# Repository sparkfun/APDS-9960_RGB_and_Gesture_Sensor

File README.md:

SparkFun APDS-9960 RGB and Gesture Sensor
========================================

[*SparkFun APDS-9960 Breakout Board (SEN-12787)*](https://www.sparkfun.com/products/12787)

This is the SparkFun RGB and Gesture Sensor, a small breakout board with a built in APDS-9960 sensor that offers ambient light and color measuring, proximity detection, and touchless gesture sensing.
With this RGB and Gesture Sensor you will be able to control a computer, microcontroller, robot, and more with a simple swipe of your hand! 

 Repository Contents
-------------------

* **/Hardware** - Eagle design files (.brd, .sch)
* **/Libraries** - Libraries for use with the SparkFun APDS9960 RGB and Gesture Sensor
* **/Production** - Production panel files (.brd)

Documentation
--------------
* **[Quickstart Guide](https://learn.sparkfun.com/tutorials/apds-9960-rgb-and-gesture-sensor-hookup-guide)** - Basic hookup guide for the sensor.
* **[Library/README](https://github.com/sparkfun/SparkFun_APDS-9960_Sensor_Arduino_Library/tree/V_1.4.1)** - Arduino library for the SparkFun_APDS9960 RGB and Gesture Sensor.
* **[SparkFun Fritzing repo](https://github.com/sparkfun/Fritzing_Parts)** - Fritzing diagrams for SparkFun products.
* **[SparkFun 3D Model repo](https://github.com/sparkfun/3D_Models)** - 3D models of SparkFun products. 

Product Versions
----------------
* **[SEN-12787](https://www.sparkfun.com/products/12787)** - APDS-9960 RGB and Gesture Sensor

Version History
---------------
* [V_H1.0_L1.4.2](https://github.com/sparkfun/APDS-9960_RGB_and_Gesture_Sensor/tree/V_H1.0_L1.4.2) - Fixing library name compiliation error. 
* [V_H1.0_L1.4.1](https://github.com/sparkfun/APDS-9960_RGB_and_Gesture_Sensor/tree/V_H1.0_L1.4.1) - Fixing minor typos in both library and hardware files.
* [V_1.1.1](https://github.com/sparkfun/APDS-9960_RGB_and_Gesture_Sensor/tree/V_1.1.1) - Updated to new tag syntax
* [V11](https://github.com/sparkfun/APDS-9960_RGB_and_Gesture_Sensor/tree/v11) - Updated to new library structure
* [v10](https://github.com/sparkfun/APDS-9960_RGB_and_Gesture_Sensor/tree/v10) - Release
* [v01](https://github.com/sparkfun/APDS-9960_RGB_and_Gesture_Sensor/tree/v01)

License Information
-------------------
This product is _**open source**_! 

The **hardware** is released under [Creative Commons ShareAlike 4.0 International](https://creativecommons.org/licenses/by-sa/4.0/).

The **code** is beerware; if you see me (or any other SparkFun employee) at the local, and you've found our code helpful, please buy us a round!

Please use, reuse, and modify these files as you see fit. Please maintain attribution to SparkFun Electronics and release anything derivative under the same license.

Distributed as-is; no warranty is given.

- Your friends at SparkFun.

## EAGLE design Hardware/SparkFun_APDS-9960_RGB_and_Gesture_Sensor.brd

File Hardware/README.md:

# What Are these Files?

The .sch and .brd files hare are Eagle CAD schematic and PCB design files.

These files were created with Eagle 6.5.0, you'll need Eagle 6.5 or later to open them up. There is a free, lite, version of Eagle available from [cadsoftusa.com](cadsoftusa.com).

# License

This product is open source! These Eagle files are released under the Creative Commons Share-Alike Attribution license ([CC BY-SA 3.0](http://creativecommons.org/licenses/by-sa/3.0/us/)).

Please use, reuse, and modify these files as you see fit. Please maintain attribution and release anything derivative under the same license.

- Your friends at SparkFun.

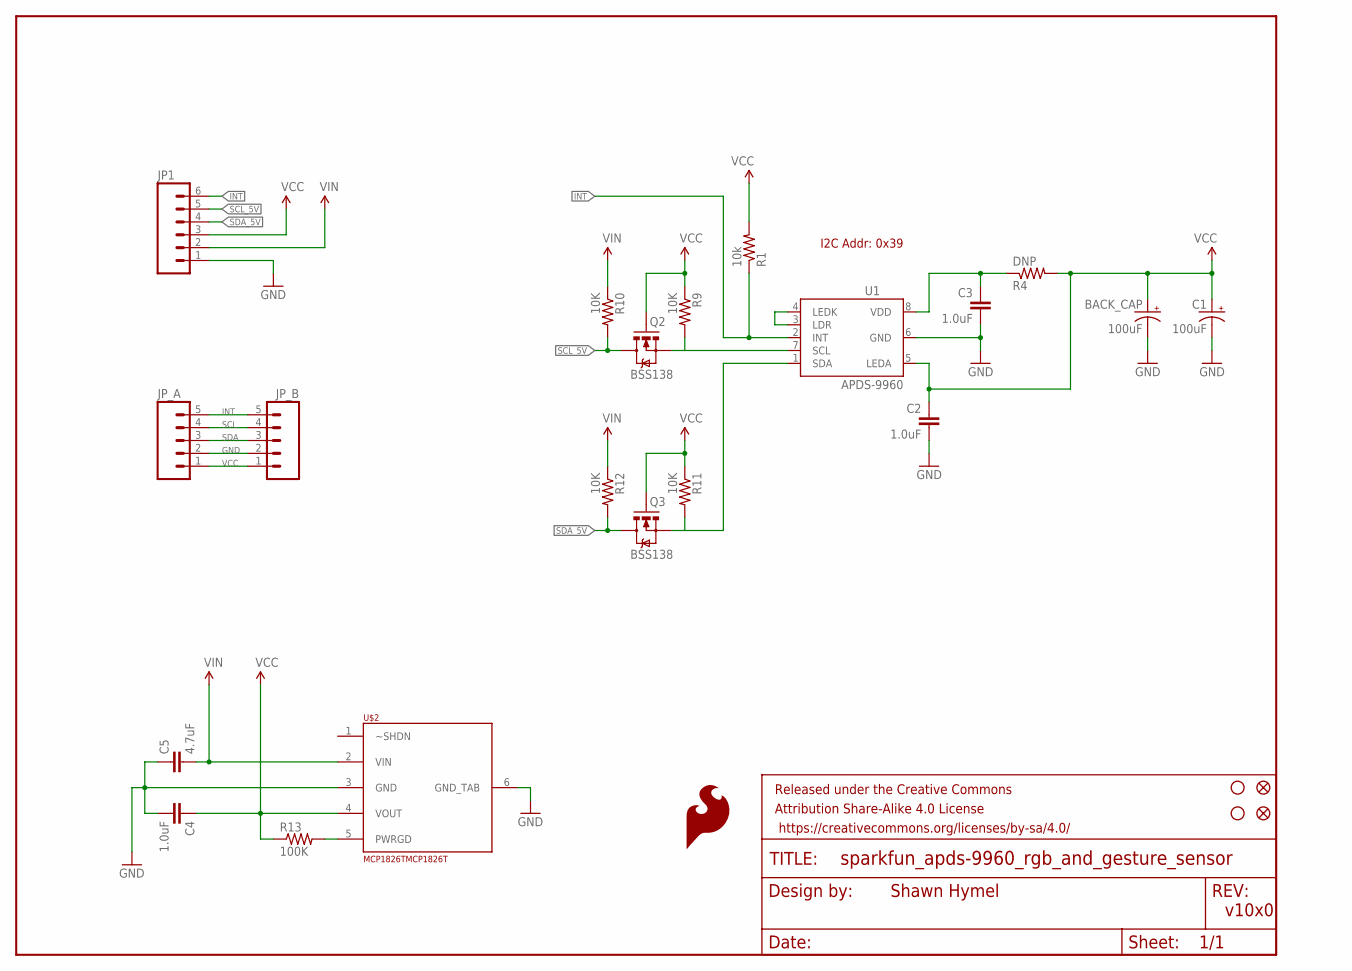
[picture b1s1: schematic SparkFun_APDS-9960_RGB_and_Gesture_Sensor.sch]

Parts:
BACK_CAP: 100uF; EIA7343
C1: 100uF; EIA7343
C2, C3, C4: 1.0uF; 0603-CAP
C5: 4.7uF; 0603-CAP
FID1, FID2: FIDUCIAL1X2; FIDUCIAL-1X2
FRAME1: FRAME-LETTER; CREATIVE_COMMONS
JP1: M06SIP; 1X06
JP_A: M05PTH; 1X05
JP_B: M05PTH; 1X05
LOGO1: SFE_LOGO_FLAME.1_INCH; SFE_LOGO_FLAME_.1
Q2, Q3: BSS138; SOT23-3
R1: 10k; 0603-RES
R4: DNP; 0603-RES
R9, R10, R11, R12: 10K; 0603-RES
R13: 100K; 0603-RES
STANDOFF1, STANDOFF2: STAND-OFF
U1: APDS-9960
U$2: MCP1826TMCP1826T; SOP-223-5

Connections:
GND: BACK_CAP.C (-), C1.C (-), C2.2, C3.2, C4.2, C5.1, JP1.1, JP_A.2, JP_B.2, U1.6 (GND), U$2.3 (GND), U$2.6 (GND_TAB)
INT: JP1.6, JP_A.5, JP_B.5, R1.1, U1.2 (INT)
unnamed: C3.1, R4.1, U1.8 (VDD)
unnamed: U1.3 (LDR), U1.4 (LEDK)
unnamed: R13.2, U$2.5 (PWRGD)
SCL: JP_A.4, JP_B.4, Q2.2 (S), R9.2, U1.7 (SCL)
SCL_5V: JP1.5, Q2.3 (D), R10.2
SDA: JP_A.3, JP_B.3, Q3.2 (S), R11.2, U1.1 (SDA)
SDA_5V: JP1.4, Q3.3 (D), R12.2
VCC: BACK_CAP.A (+), C1.A (+), C2.1, C4.1, JP1.3, JP_A.1, JP_B.1, Q2.1 (G), Q3.1 (G), R1.2, R4.2, R9.1, R11.1, R13.1, U1.5 (LEDA), U$2.4 (VOUT)
VIN: C5.2, JP1.2, R10.1, R12.1, U$2.2 (VIN)

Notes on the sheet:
v10x0
Shawn Hymel
I2C Addr: 0x39

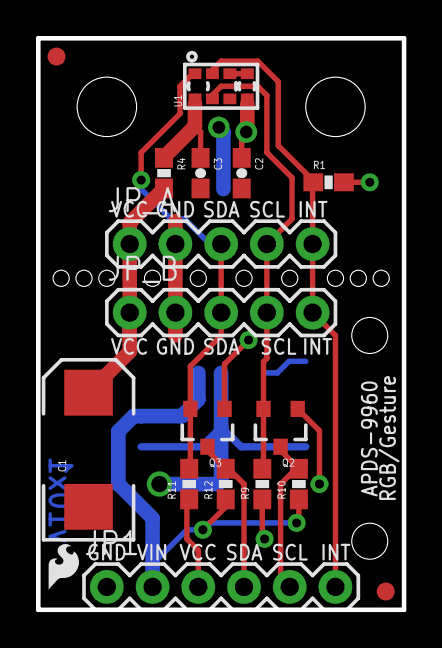
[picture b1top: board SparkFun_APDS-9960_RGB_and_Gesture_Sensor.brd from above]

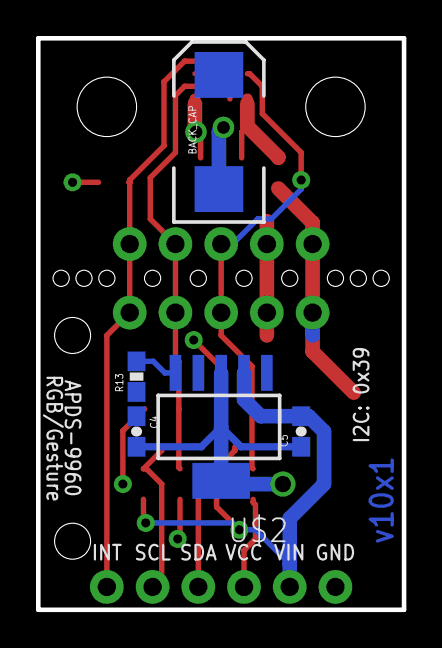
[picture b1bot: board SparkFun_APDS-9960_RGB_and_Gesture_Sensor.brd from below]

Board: 2 copper layers, 20.3 x 31.8 mm, 26 parts (5 on the bottom side), 11 nets.

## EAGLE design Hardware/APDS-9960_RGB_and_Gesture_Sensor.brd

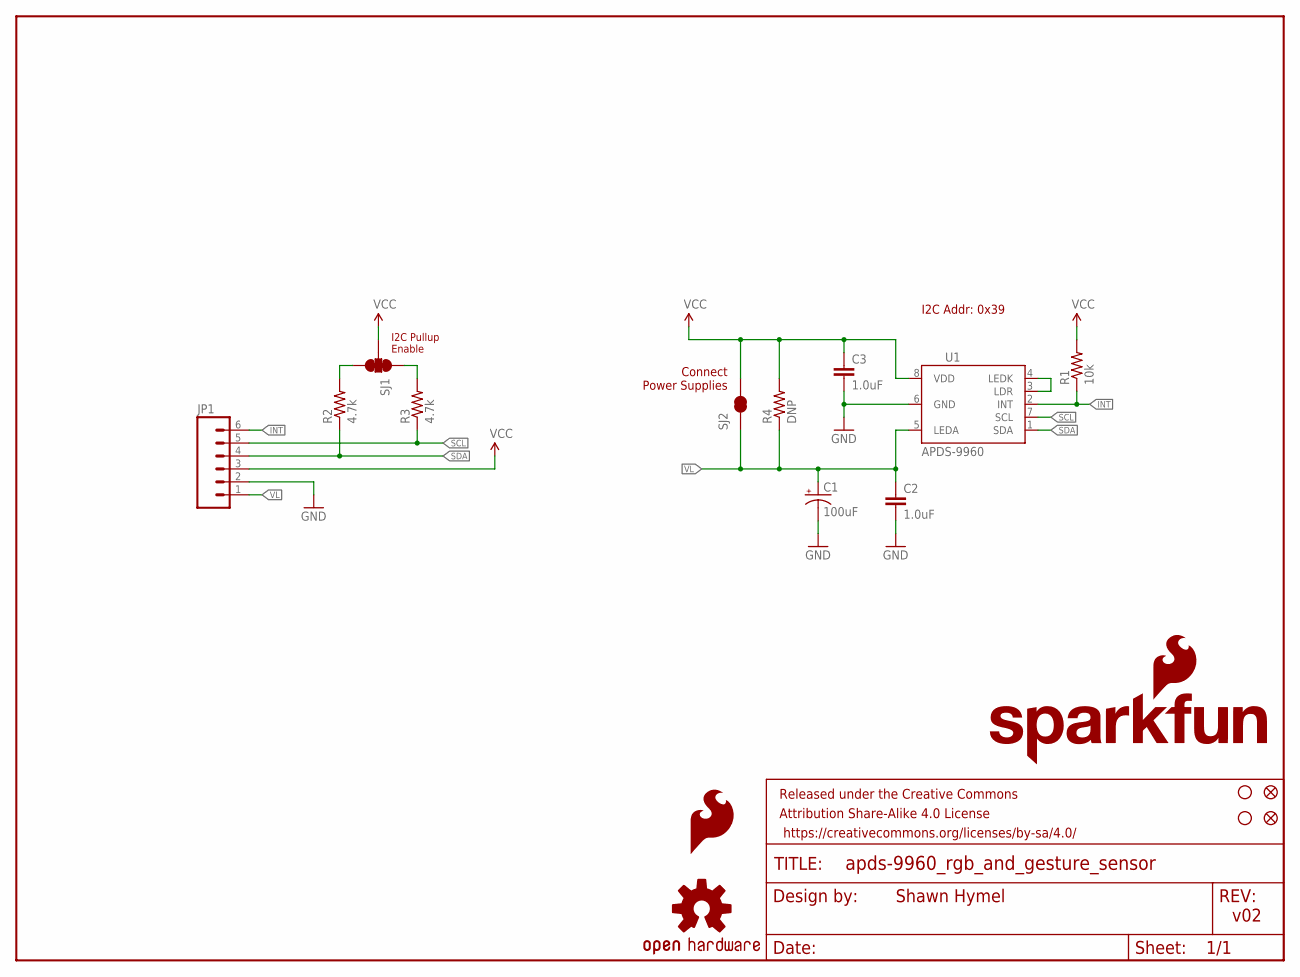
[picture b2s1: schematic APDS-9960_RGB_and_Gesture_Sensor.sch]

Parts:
C1: 100uF; EIA7343
C2, C3: 1.0uF; 0603-CAP
FID1, FID2: FIDUCIAL1X2; FIDUCIAL-1X2
FRAME1: FRAME-LETTER; CREATIVE_COMMONS
JP1: M06SIP; 1X06
LOGO1: SFE_LOGO_FLAME.1_INCH; SFE_LOGO_FLAME_.1
LOGO2: OSHW-LOGOS; OSHW-LOGO-S
R1: 10k; 0603-RES
R2, R3: 4.7k; 0603
R4: DNP; 0603-RES
SJ1: SOLDERJUMPER_2WAYPASTE1&2&3; SJ_3_PASTE1&2&3
SJ2: SOLDERJUMPERNC; SJ_2S
STANDOFF1, STANDOFF2: STAND-OFF
U1: APDS-9960
U$1: SFE_LOGO_NAME_FLAME.1_INCH; SFE_LOGO_NAME_FLAME_.1

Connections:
GND: C1.C (-), C2.2, C3.2, JP1.2, U1.6 (GND)
INT: JP1.6, R1.1, U1.2 (INT)
unnamed: R2.2, SJ1.3
unnamed: R3.2, SJ1.1
unnamed: U1.3 (LDR), U1.4 (LEDK)
SCL: JP1.5, R3.1, U1.7 (SCL)
SDA: JP1.4, R2.1, U1.1 (SDA)
VCC: C3.1, JP1.3, R1.2, R4.2, SJ1.2, SJ2.2, U1.8 (VDD)
VL: C1.A (+), C2.1, JP1.1, R4.1, SJ2.1, U1.5 (LEDA)

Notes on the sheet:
v02
Shawn Hymel
I2C Addr: 0x39
I2C Pullup Enable
Connect Power Supplies

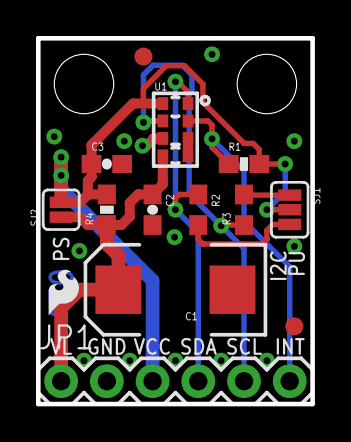
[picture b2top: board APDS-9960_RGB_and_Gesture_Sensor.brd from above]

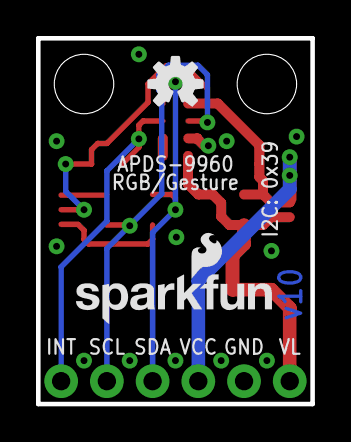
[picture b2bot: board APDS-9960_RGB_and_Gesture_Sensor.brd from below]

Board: 2 copper layers, 15.2 x 20.3 mm, 19 parts (2 on the bottom side), 9 nets.

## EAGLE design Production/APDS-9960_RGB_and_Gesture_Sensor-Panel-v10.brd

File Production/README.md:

These are the production files SparkFun uses for printing PCBs, as well as the Eagle files for our test beds.

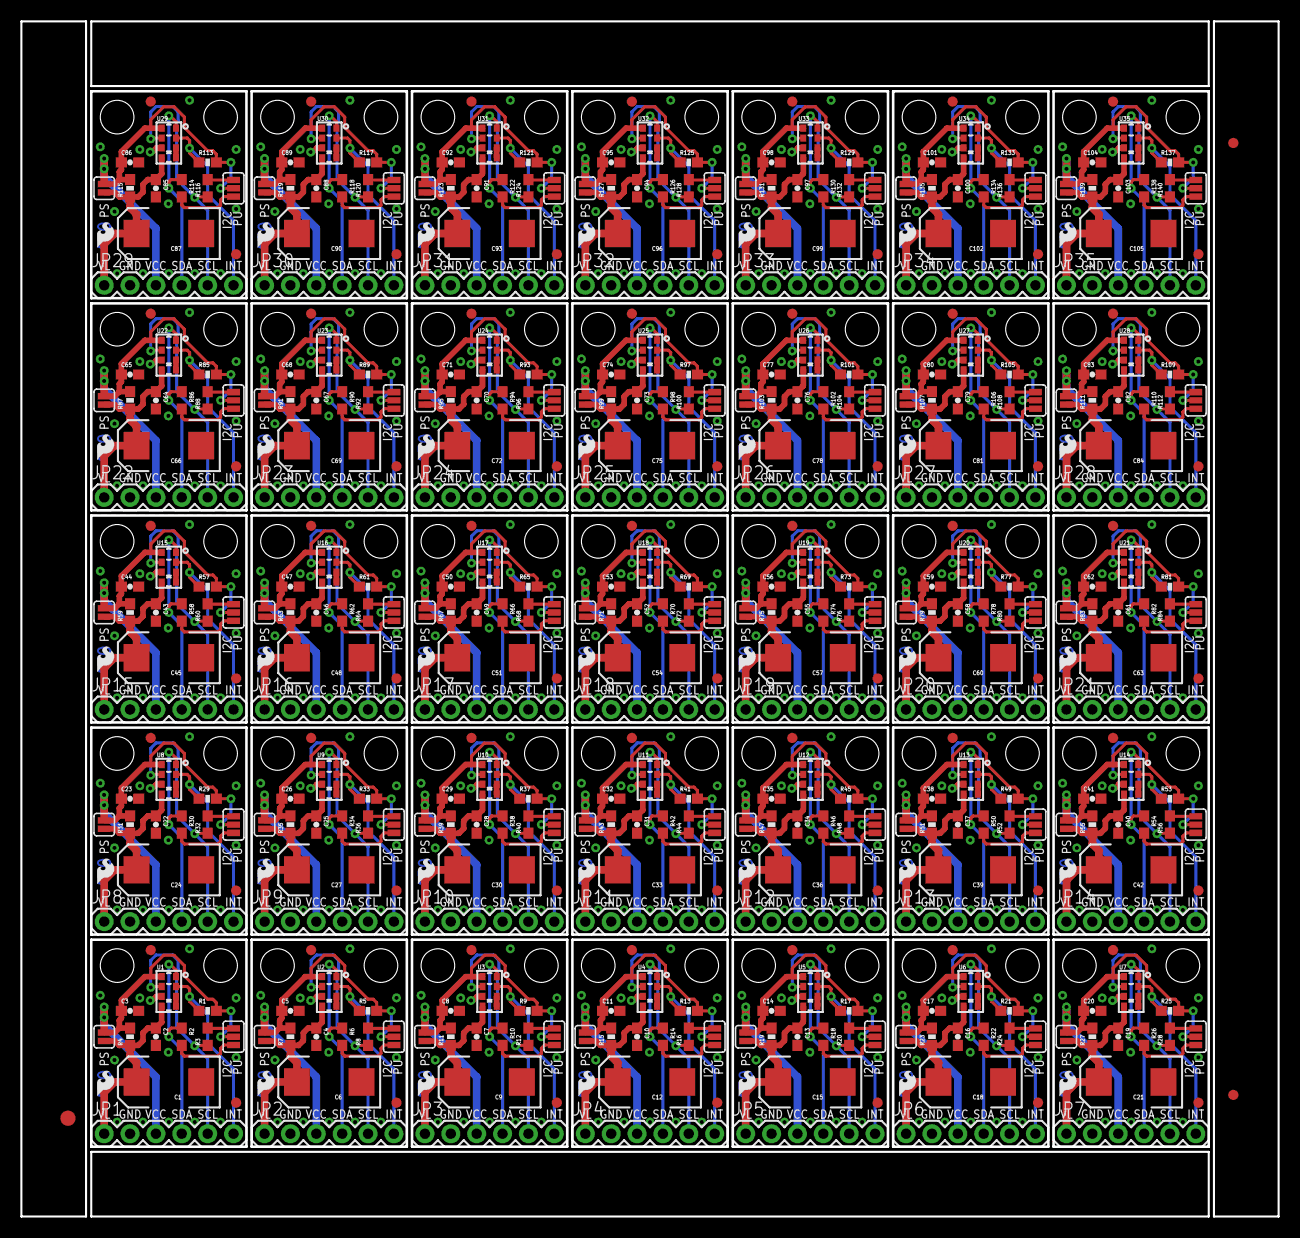
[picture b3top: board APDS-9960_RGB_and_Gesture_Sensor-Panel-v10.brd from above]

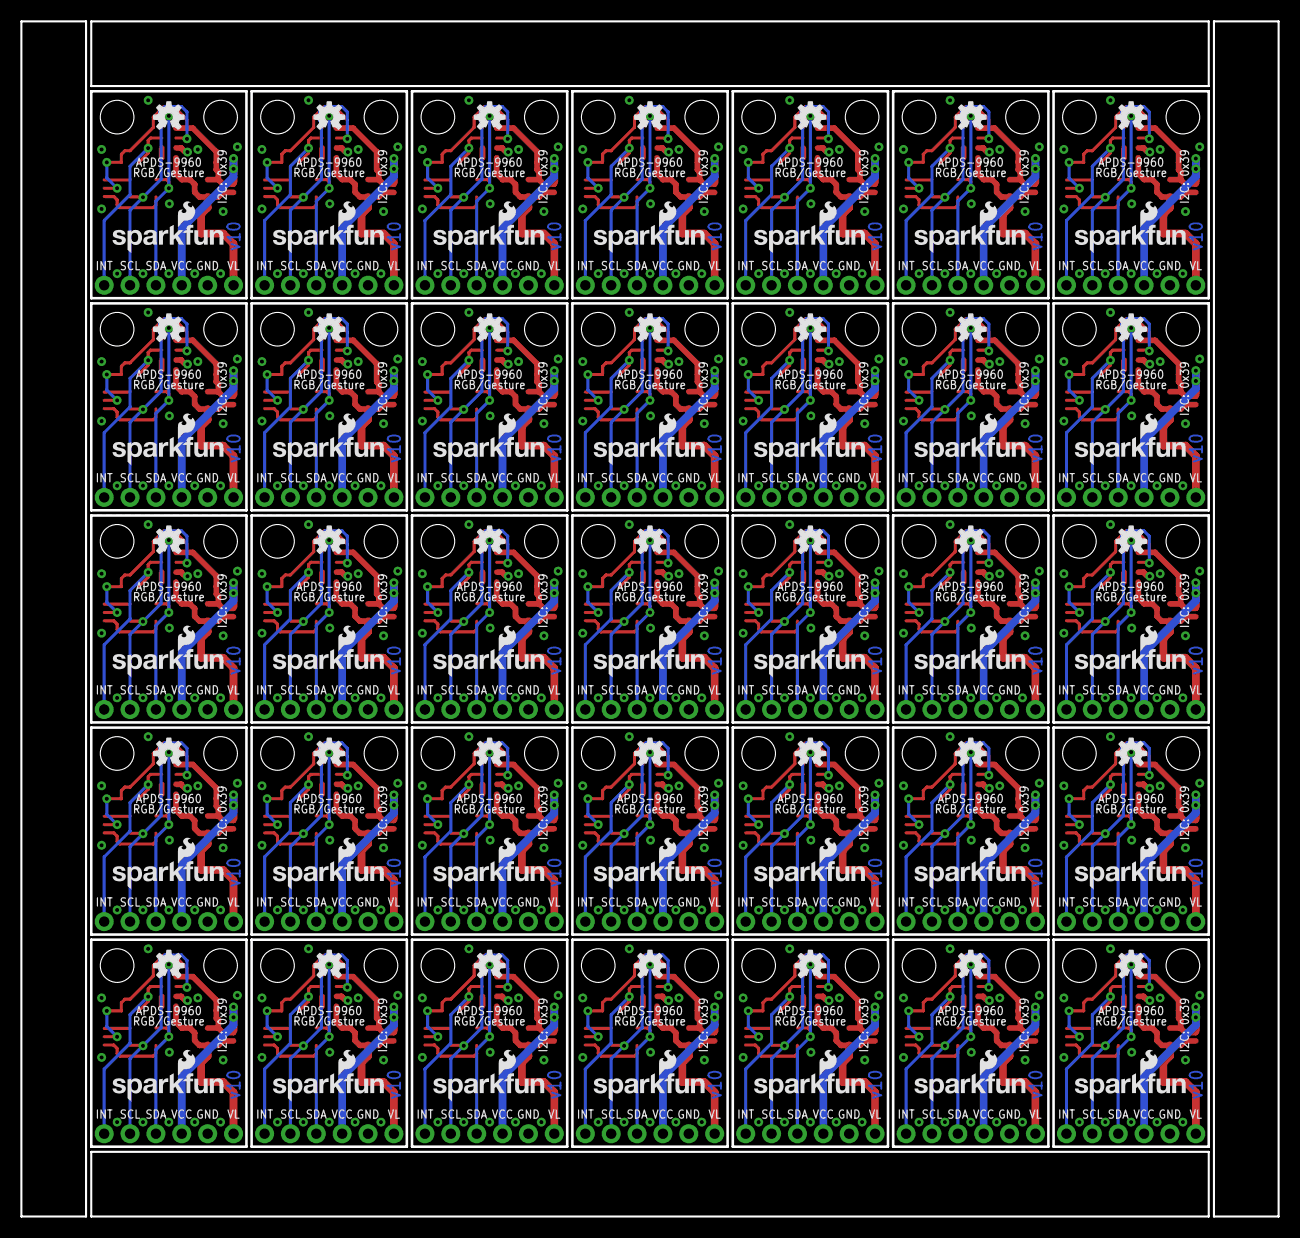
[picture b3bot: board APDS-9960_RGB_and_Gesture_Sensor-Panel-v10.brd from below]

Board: 2 copper layers, 123.4 x 117.3 mm, 633 parts (70 on the bottom side), 315 nets.

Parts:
C1, C6, C9, C12, C15, C18, C21, C24, C27, C30, C33, C36, C39, C42, C45, C48, C51, C54, C57, C60, C63, C66, C69, C72, C75, C78, C81, C84, C87, C90, C93, C96, C99, C102, C105: 100uF; EIA7343
C2, C3, C4, C5, C7, C8, C10, C11, C13, C14, C16, C17, C19, C20, C22, C23, C25, C26, C28, C29, C31, C32, C34, C35, C37, C38, C40, C41, C43, C44, C46, C47, C49, C50, C52, C53, C55, C56, C58, C59, C61, C62, C64, C65, C67, C68, C70, C71, C73, C74, C76, C77, C79, C80, C82, C83, C85, C86, C88, C89, C91, C92, C94, C95, C97, C98, C100, C101, C103, C104: 1.0uF; 0603-CAP
E$1: FIDUCIAL-1.5X3
E$4, E$6: FIDUCIAL-1X2
FID1, FID2, FID3, FID4, FID5, FID6, FID7, FID8, FID9, FID10, FID11, FID12, FID13, FID14, FID15, FID16, FID17, FID18, FID19, FID20, FID21, FID22, FID23, FID24, FID25, FID26, FID27, FID28, FID29, FID30, FID31, FID32, FID33, FID34, FID35, FID36, FID37, FID38, FID39, FID40, FID41, FID42, FID43, FID44, FID45, FID46, FID47, FID48, FID49, FID50, FID51, FID52, FID53, FID54, FID55, FID56, FID57, FID58, FID59, FID60, FID61, FID62, FID63, FID64, FID65, FID66, FID67, FID68, FID69, FID70: FIDUCIAL1X2; FIDUCIAL-1X2
JP1, JP2, JP3, JP4, JP5, JP6, JP7, JP8, JP9, JP10, JP11, JP12, JP13, JP14, JP15, JP16, JP17, JP18, JP19, JP20, JP21, JP22, JP23, JP24, JP25, JP26, JP27, JP28, JP29, JP30, JP31, JP32, JP33, JP34, JP35: 1X06
LOGO1, LOGO3, LOGO5, LOGO7, LOGO9, LOGO11, LOGO13, LOGO15, LOGO17, LOGO19, LOGO21, LOGO23, LOGO25, LOGO27, LOGO29, LOGO31, LOGO33, LOGO35, LOGO37, LOGO39, LOGO41, LOGO43, LOGO45, LOGO47, LOGO49, LOGO51, LOGO53, LOGO55, LOGO57, LOGO59, LOGO61, LOGO63, LOGO65, LOGO67, LOGO69: SFE_LOGO_FLAME.1_INCH; SFE_LOGO_FLAME_.1
LOGO2, LOGO4, LOGO6, LOGO8, LOGO10, LOGO12, LOGO14, LOGO16, LOGO18, LOGO20, LOGO22, LOGO24, LOGO26, LOGO28, LOGO30, LOGO32, LOGO34, LOGO36, LOGO38, LOGO40, LOGO42, LOGO44, LOGO46, LOGO48, LOGO50, LOGO52, LOGO54, LOGO56, LOGO58, LOGO60, LOGO62, LOGO64, LOGO66, LOGO68, LOGO70: OSHW-LOGOS; OSHW-LOGO-S
R1, R5, R9, R13, R17, R21, R25, R29, R33, R37, R41, R45, R49, R53, R57, R61, R65, R69, R73, R77, R81, R85, R89, R93, R97, R101, R105, R109, R113, R117, R121, R125, R129, R133, R137: 10k; 0603-RES
R2, R3, R6, R8, R10, R12, R14, R16, R18, R20, R22, R24, R26, R28, R30, R32, R34, R36, R38, R40, R42, R44, R46, R48, R50, R52, R54, R56, R58, R60, R62, R64, R66, R68, R70, R72, R74, R76, R78, R80, R82, R84, R86, R88, R90, R92, R94, R96, R98, R100, R102, R104, R106, R108, R110, R112, R114, R116, R118, R120, R122, R124, R126, R128, R130, R132, R134, R136, R138, R140: 4.7k; 0603
R4, R7, R11, R15, R19, R23, R27, R31, R35, R39, R43, R47, R51, R55, R59, R63, R67, R71, R75, R79, R83, R87, R91, R95, R99, R103, R107, R111, R115, R119, R123, R127, R131, R135, R139: DNP; 0603-RES
SJ1, SJ3, SJ5, SJ7, SJ9, SJ11, SJ13, SJ15, SJ17, SJ19, SJ21, SJ23, SJ25, SJ27, SJ29, SJ31, SJ33, SJ35, SJ37, SJ39, SJ41, SJ43, SJ45, SJ47, SJ49, SJ51, SJ53, SJ55, SJ57, SJ59, SJ61, SJ63, SJ65, SJ67, SJ69: SJ_3_PASTE1&2&3
SJ2, SJ4, SJ6, SJ8, SJ10, SJ12, SJ14, SJ16, SJ18, SJ20, SJ22, SJ24, SJ26, SJ28, SJ30, SJ32, SJ34, SJ36, SJ38, SJ40, SJ42, SJ44, SJ46, SJ48, SJ50, SJ52, SJ54, SJ56, SJ58, SJ60, SJ62, SJ64, SJ66, SJ68, SJ70: SOLDERJUMPERNC; SJ_2S
STANDOFF1, STANDOFF2, STANDOFF3, STANDOFF4, STANDOFF5, STANDOFF6, STANDOFF7, STANDOFF8, STANDOFF9, STANDOFF10, STANDOFF11, STANDOFF12, STANDOFF13, STANDOFF14, STANDOFF15, STANDOFF16, STANDOFF17, STANDOFF18, STANDOFF19, STANDOFF20, STANDOFF21, STANDOFF22, STANDOFF23, STANDOFF24, STANDOFF25, STANDOFF26, STANDOFF27, STANDOFF28, STANDOFF29, STANDOFF30, STANDOFF31, STANDOFF32, STANDOFF33, STANDOFF34, STANDOFF35, STANDOFF36, STANDOFF37, STANDOFF38, STANDOFF39, STANDOFF40, STANDOFF41, STANDOFF42, STANDOFF43, STANDOFF44, STANDOFF45, STANDOFF46, STANDOFF47, STANDOFF48, STANDOFF49, STANDOFF50, STANDOFF51, STANDOFF52, STANDOFF53, STANDOFF54, STANDOFF55, STANDOFF56, STANDOFF57, STANDOFF58, STANDOFF59, STANDOFF60, STANDOFF61, STANDOFF62, STANDOFF63, STANDOFF64, STANDOFF65, STANDOFF66, STANDOFF67, STANDOFF68, STANDOFF69, STANDOFF70: STAND-OFF
U1, U2, U3, U4, U5, U6, U7, U8, U9, U10, U11, U12, U13, U14, U15, U16, U17, U18, U19, U20, U21, U22, U23, U24, U25, U26, U27, U28, U29, U30, U31, U32, U33, U34, U35: APDS-9960
U$1, U$2, U$3, U$4, U$5, U$6, U$7, U$8, U$9, U$10, U$11, U$12, U$13, U$14, U$15, U$16, U$17, U$18, U$19, U$20, U$21, U$22, U$23, U$24, U$25, U$26, U$27, U$28, U$29, U$30, U$31, U$32, U$33, U$34, U$35: SFE_LOGO_NAME_FLAME.1_INCH; SFE_LOGO_NAME_FLAME_.1

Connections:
GND: C1.C, C2.2, C3.2, JP1.2, U1.6
GND1: C4.2, C5.2, C6.C, JP2.2, U2.6
GND2: C7.2, C8.2, C9.C, JP3.2, U3.6
GND3: C10.2, C11.2, C12.C, JP4.2, U4.6
GND4: C13.2, C14.2, C15.C, JP5.2, U5.6
GND5: C16.2, C17.2, C18.C, JP6.2, U6.6
GND6: C19.2, C20.2, C21.C, JP7.2, U7.6
GND7: C22.2, C23.2, C24.C, JP8.2, U8.6
GND8: C25.2, C26.2, C27.C, JP9.2, U9.6
GND9: C28.2, C29.2, C30.C, JP10.2, U10.6
GND10: C31.2, C32.2, C33.C, JP11.2, U11.6
GND11: C34.2, C35.2, C36.C, JP12.2, U12.6
GND12: C37.2, C38.2, C39.C, JP13.2, U13.6
GND13: C40.2, C41.2, C42.C, JP14.2, U14.6
GND14: C43.2, C44.2, C45.C, JP15.2, U15.6
GND15: C46.2, C47.2, C48.C, JP16.2, U16.6
GND16: C49.2, C50.2, C51.C, JP17.2, U17.6
GND17: C52.2, C53.2, C54.C, JP18.2, U18.6
GND18: C55.2, C56.2, C57.C, JP19.2, U19.6
GND19: C58.2, C59.2, C60.C, JP20.2, U20.6
GND20: C61.2, C62.2, C63.C, JP21.2, U21.6
GND21: C64.2, C65.2, C66.C, JP22.2, U22.6
GND22: C67.2, C68.2, C69.C, JP23.2, U23.6
GND23: C70.2, C71.2, C72.C, JP24.2, U24.6
GND24: C73.2, C74.2, C75.C, JP25.2, U25.6
GND25: C76.2, C77.2, C78.C, JP26.2, U26.6
GND26: C79.2, C80.2, C81.C, JP27.2, U27.6
GND27: C82.2, C83.2, C84.C, JP28.2, U28.6
GND28: C85.2, C86.2, C87.C, JP29.2, U29.6
GND29: C88.2, C89.2, C90.C, JP30.2, U30.6
GND30: C91.2, C92.2, C93.C, JP31.2, U31.6
GND31: C94.2, C95.2, C96.C, JP32.2, U32.6
GND32: C97.2, C98.2, C99.C, JP33.2, U33.6
GND33: C100.2, C101.2, C102.C, JP34.2, U34.6
GND34: C103.2, C104.2, C105.C, JP35.2, U35.6
INT: JP1.6, R1.1, U1.2
INT1: JP2.6, R5.1, U2.2
INT2: JP3.6, R9.1, U3.2
INT3: JP4.6, R13.1, U4.2
INT4: JP5.6, R17.1, U5.2
INT5: JP6.6, R21.1, U6.2
INT6: JP7.6, R25.1, U7.2
INT7: JP8.6, R29.1, U8.2
INT8: JP9.6, R33.1, U9.2
INT9: JP10.6, R37.1, U10.2
INT10: JP11.6, R41.1, U11.2
INT11: JP12.6, R45.1, U12.2
INT12: JP13.6, R49.1, U13.2
INT13: JP14.6, R53.1, U14.2
INT14: JP15.6, R57.1, U15.2
INT15: JP16.6, R61.1, U16.2
INT16: JP17.6, R65.1, U17.2
INT17: JP18.6, R69.1, U18.2
INT18: JP19.6, R73.1, U19.2
INT19: JP20.6, R77.1, U20.2
INT20: JP21.6, R81.1, U21.2
INT21: JP22.6, R85.1, U22.2
INT22: JP23.6, R89.1, U23.2
INT23: JP24.6, R93.1, U24.2
INT24: JP25.6, R97.1, U25.2
INT25: JP26.6, R101.1, U26.2
INT26: JP27.6, R105.1, U27.2
INT27: JP28.6, R109.1, U28.2
INT28: JP29.6, R113.1, U29.2
INT29: JP30.6, R117.1, U30.2
INT30: JP31.6, R121.1, U31.2
INT31: JP32.6, R125.1, U32.2
INT32: JP33.6, R129.1, U33.2
INT33: JP34.6, R133.1, U34.2
INT34: JP35.6, R137.1, U35.2
unnamed: R2.2, SJ1.3
unnamed: R3.2, SJ1.1
unnamed: U1.3, U1.4
unnamed: R6.2, SJ3.3
unnamed: R8.2, SJ3.1
unnamed: U2.3, U2.4
unnamed: R10.2, SJ5.3
unnamed: R12.2, SJ5.1
unnamed: U3.3, U3.4
unnamed: R14.2, SJ7.3
unnamed: R16.2, SJ7.1
unnamed: U4.3, U4.4
unnamed: R18.2, SJ9.3
unnamed: R20.2, SJ9.1
unnamed: U5.3, U5.4
unnamed: R22.2, SJ11.3
unnamed: R24.2, SJ11.1
unnamed: U6.3, U6.4
unnamed: R26.2, SJ13.3
unnamed: R28.2, SJ13.1
unnamed: U7.3, U7.4
unnamed: R30.2, SJ15.3
unnamed: R32.2, SJ15.1
unnamed: U8.3, U8.4
unnamed: R34.2, SJ17.3
unnamed: R36.2, SJ17.1
unnamed: U9.3, U9.4
unnamed: R38.2, SJ19.3
unnamed: R40.2, SJ19.1
unnamed: U10.3, U10.4
unnamed: R42.2, SJ21.3
unnamed: R44.2, SJ21.1
unnamed: U11.3, U11.4
unnamed: R46.2, SJ23.3
unnamed: R48.2, SJ23.1
unnamed: U12.3, U12.4
unnamed: R50.2, SJ25.3
unnamed: R52.2, SJ25.1
unnamed: U13.3, U13.4
unnamed: R54.2, SJ27.3
unnamed: R56.2, SJ27.1
unnamed: U14.3, U14.4
unnamed: R58.2, SJ29.3
unnamed: R60.2, SJ29.1
unnamed: U15.3, U15.4
unnamed: R62.2, SJ31.3
unnamed: R64.2, SJ31.1
unnamed: U16.3, U16.4
unnamed: R66.2, SJ33.3
unnamed: R68.2, SJ33.1
unnamed: U17.3, U17.4
unnamed: R70.2, SJ35.3
unnamed: R72.2, SJ35.1
unnamed: U18.3, U18.4
unnamed: R74.2, SJ37.3
unnamed: R76.2, SJ37.1
unnamed: U19.3, U19.4
unnamed: R78.2, SJ39.3
unnamed: R80.2, SJ39.1
unnamed: U20.3, U20.4
unnamed: R82.2, SJ41.3
unnamed: R84.2, SJ41.1
unnamed: U21.3, U21.4
unnamed: R86.2, SJ43.3
unnamed: R88.2, SJ43.1
unnamed: U22.3, U22.4
unnamed: R90.2, SJ45.3
unnamed: R92.2, SJ45.1
unnamed: U23.3, U23.4
unnamed: R94.2, SJ47.3
unnamed: R96.2, SJ47.1
unnamed: U24.3, U24.4
unnamed: R98.2, SJ49.3
unnamed: R100.2, SJ49.1
unnamed: U25.3, U25.4
unnamed: R102.2, SJ51.3
unnamed: R104.2, SJ51.1
unnamed: U26.3, U26.4
unnamed: R106.2, SJ53.3
unnamed: R108.2, SJ53.1
unnamed: U27.3, U27.4
unnamed: R110.2, SJ55.3
unnamed: R112.2, SJ55.1
unnamed: U28.3, U28.4
unnamed: R114.2, SJ57.3
unnamed: R116.2, SJ57.1
unnamed: U29.3, U29.4
unnamed: R118.2, SJ59.3
unnamed: R120.2, SJ59.1
unnamed: U30.3, U30.4
unnamed: R122.2, SJ61.3
unnamed: R124.2, SJ61.1
unnamed: U31.3, U31.4
unnamed: R126.2, SJ63.3
unnamed: R128.2, SJ63.1
unnamed: U32.3, U32.4
unnamed: R130.2, SJ65.3
unnamed: R132.2, SJ65.1
unnamed: U33.3, U33.4
unnamed: R134.2, SJ67.3
unnamed: R136.2, SJ67.1
unnamed: U34.3, U34.4
unnamed: R138.2, SJ69.3
unnamed: R140.2, SJ69.1
unnamed: U35.3, U35.4
SCL: JP1.5, R3.1, U1.7
SCL1: JP2.5, R8.1, U2.7
SCL2: JP3.5, R12.1, U3.7
SCL3: JP4.5, R16.1, U4.7
SCL4: JP5.5, R20.1, U5.7
SCL5: JP6.5, R24.1, U6.7
SCL6: JP7.5, R28.1, U7.7
SCL7: JP8.5, R32.1, U8.7
SCL8: JP9.5, R36.1, U9.7
SCL9: JP10.5, R40.1, U10.7
SCL10: JP11.5, R44.1, U11.7
SCL11: JP12.5, R48.1, U12.7
SCL12: JP13.5, R52.1, U13.7
SCL13: JP14.5, R56.1, U14.7
SCL14: JP15.5, R60.1, U15.7
SCL15: JP16.5, R64.1, U16.7
SCL16: JP17.5, R68.1, U17.7
SCL17: JP18.5, R72.1, U18.7
SCL18: JP19.5, R76.1, U19.7
SCL19: JP20.5, R80.1, U20.7
SCL20: JP21.5, R84.1, U21.7
SCL21: JP22.5, R88.1, U22.7
SCL22: JP23.5, R92.1, U23.7
SCL23: JP24.5, R96.1, U24.7
SCL24: JP25.5, R100.1, U25.7
SCL25: JP26.5, R104.1, U26.7
SCL26: JP27.5, R108.1, U27.7
SCL27: JP28.5, R112.1, U28.7
SCL28: JP29.5, R116.1, U29.7
SCL29: JP30.5, R120.1, U30.7
SCL30: JP31.5, R124.1, U31.7
SCL31: JP32.5, R128.1, U32.7
SCL32: JP33.5, R132.1, U33.7
SCL33: JP34.5, R136.1, U34.7
SCL34: JP35.5, R140.1, U35.7
SDA: JP1.4, R2.1, U1.1
SDA1: JP2.4, R6.1, U2.1
SDA2: JP3.4, R10.1, U3.1
SDA3: JP4.4, R14.1, U4.1
SDA4: JP5.4, R18.1, U5.1
SDA5: JP6.4, R22.1, U6.1
SDA6: JP7.4, R26.1, U7.1
SDA7: JP8.4, R30.1, U8.1
SDA8: JP9.4, R34.1, U9.1
SDA9: JP10.4, R38.1, U10.1
SDA10: JP11.4, R42.1, U11.1
SDA11: JP12.4, R46.1, U12.1
SDA12: JP13.4, R50.1, U13.1
SDA13: JP14.4, R54.1, U14.1
SDA14: JP15.4, R58.1, U15.1
SDA15: JP16.4, R62.1, U16.1
SDA16: JP17.4, R66.1, U17.1
SDA17: JP18.4, R70.1, U18.1
SDA18: JP19.4, R74.1, U19.1
SDA19: JP20.4, R78.1, U20.1
SDA20: JP21.4, R82.1, U21.1
SDA21: JP22.4, R86.1, U22.1
SDA22: JP23.4, R90.1, U23.1
SDA23: JP24.4, R94.1, U24.1
SDA24: JP25.4, R98.1, U25.1
SDA25: JP26.4, R102.1, U26.1
SDA26: JP27.4, R106.1, U27.1
SDA27: JP28.4, R110.1, U28.1
SDA28: JP29.4, R114.1, U29.1
SDA29: JP30.4, R118.1, U30.1
SDA30: JP31.4, R122.1, U31.1
SDA31: JP32.4, R126.1, U32.1
SDA32: JP33.4, R130.1, U33.1
SDA33: JP34.4, R134.1, U34.1
SDA34: JP35.4, R138.1, U35.1
VCC: C3.1, JP1.3, R1.2, R4.2, SJ1.2, SJ2.2, U1.8
VCC1: C5.1, JP2.3, R5.2, R7.2, SJ3.2, SJ4.2, U2.8
VCC2: C8.1, JP3.3, R9.2, R11.2, SJ5.2, SJ6.2, U3.8
VCC3: C11.1, JP4.3, R13.2, R15.2, SJ7.2, SJ8.2, U4.8
VCC4: C14.1, JP5.3, R17.2, R19.2, SJ9.2, SJ10.2, U5.8
VCC5: C17.1, JP6.3, R21.2, R23.2, SJ11.2, SJ12.2, U6.8
VCC6: C20.1, JP7.3, R25.2, R27.2, SJ13.2, SJ14.2, U7.8
VCC7: C23.1, JP8.3, R29.2, R31.2, SJ15.2, SJ16.2, U8.8
VCC8: C26.1, JP9.3, R33.2, R35.2, SJ17.2, SJ18.2, U9.8
VCC9: C29.1, JP10.3, R37.2, R39.2, SJ19.2, SJ20.2, U10.8
VCC10: C32.1, JP11.3, R41.2, R43.2, SJ21.2, SJ22.2, U11.8
VCC11: C35.1, JP12.3, R45.2, R47.2, SJ23.2, SJ24.2, U12.8
VCC12: C38.1, JP13.3, R49.2, R51.2, SJ25.2, SJ26.2, U13.8
VCC13: C41.1, JP14.3, R53.2, R55.2, SJ27.2, SJ28.2, U14.8
VCC14: C44.1, JP15.3, R57.2, R59.2, SJ29.2, SJ30.2, U15.8
VCC15: C47.1, JP16.3, R61.2, R63.2, SJ31.2, SJ32.2, U16.8
VCC16: C50.1, JP17.3, R65.2, R67.2, SJ33.2, SJ34.2, U17.8
VCC17: C53.1, JP18.3, R69.2, R71.2, SJ35.2, SJ36.2, U18.8
VCC18: C56.1, JP19.3, R73.2, R75.2, SJ37.2, SJ38.2, U19.8
VCC19: C59.1, JP20.3, R77.2, R79.2, SJ39.2, SJ40.2, U20.8
VCC20: C62.1, JP21.3, R81.2, R83.2, SJ41.2, SJ42.2, U21.8
VCC21: C65.1, JP22.3, R85.2, R87.2, SJ43.2, SJ44.2, U22.8
VCC22: C68.1, JP23.3, R89.2, R91.2, SJ45.2, SJ46.2, U23.8
VCC23: C71.1, JP24.3, R93.2, R95.2, SJ47.2, SJ48.2, U24.8
VCC24: C74.1, JP25.3, R97.2, R99.2, SJ49.2, SJ50.2, U25.8
VCC25: C77.1, JP26.3, R101.2, R103.2, SJ51.2, SJ52.2, U26.8
VCC26: C80.1, JP27.3, R105.2, R107.2, SJ53.2, SJ54.2, U27.8
VCC27: C83.1, JP28.3, R109.2, R111.2, SJ55.2, SJ56.2, U28.8
VCC28: C86.1, JP29.3, R113.2, R115.2, SJ57.2, SJ58.2, U29.8
VCC29: C89.1, JP30.3, R117.2, R119.2, SJ59.2, SJ60.2, U30.8
VCC30: C92.1, JP31.3, R121.2, R123.2, SJ61.2, SJ62.2, U31.8
VCC31: C95.1, JP32.3, R125.2, R127.2, SJ63.2, SJ64.2, U32.8
VCC32: C98.1, JP33.3, R129.2, R131.2, SJ65.2, SJ66.2, U33.8
VCC33: C101.1, JP34.3, R133.2, R135.2, SJ67.2, SJ68.2, U34.8
VCC34: C104.1, JP35.3, R137.2, R139.2, SJ69.2, SJ70.2, U35.8
VL: C1.A, C2.1, JP1.1, R4.1, SJ2.1, U1.5
VL1: C4.1, C6.A, JP2.1, R7.1, SJ4.1, U2.5
VL2: C7.1, C9.A, JP3.1, R11.1, SJ6.1, U3.5
VL3: C10.1, C12.A, JP4.1, R15.1, SJ8.1, U4.5
VL4: C13.1, C15.A, JP5.1, R19.1, SJ10.1, U5.5
VL5: C16.1, C18.A, JP6.1, R23.1, SJ12.1, U6.5
VL6: C19.1, C21.A, JP7.1, R27.1, SJ14.1, U7.5
VL7: C22.1, C24.A, JP8.1, R31.1, SJ16.1, U8.5
VL8: C25.1, C27.A, JP9.1, R35.1, SJ18.1, U9.5
VL9: C28.1, C30.A, JP10.1, R39.1, SJ20.1, U10.5
VL10: C31.1, C33.A, JP11.1, R43.1, SJ22.1, U11.5
VL11: C34.1, C36.A, JP12.1, R47.1, SJ24.1, U12.5
VL12: C37.1, C39.A, JP13.1, R51.1, SJ26.1, U13.5
VL13: C40.1, C42.A, JP14.1, R55.1, SJ28.1, U14.5
VL14: C43.1, C45.A, JP15.1, R59.1, SJ30.1, U15.5
VL15: C46.1, C48.A, JP16.1, R63.1, SJ32.1, U16.5
VL16: C49.1, C51.A, JP17.1, R67.1, SJ34.1, U17.5
VL17: C52.1, C54.A, JP18.1, R71.1, SJ36.1, U18.5
VL18: C55.1, C57.A, JP19.1, R75.1, SJ38.1, U19.5
VL19: C58.1, C60.A, JP20.1, R79.1, SJ40.1, U20.5
VL20: C61.1, C63.A, JP21.1, R83.1, SJ42.1, U21.5
VL21: C64.1, C66.A, JP22.1, R87.1, SJ44.1, U22.5
VL22: C67.1, C69.A, JP23.1, R91.1, SJ46.1, U23.5
VL23: C70.1, C72.A, JP24.1, R95.1, SJ48.1, U24.5
VL24: C73.1, C75.A, JP25.1, R99.1, SJ50.1, U25.5
VL25: C76.1, C78.A, JP26.1, R103.1, SJ52.1, U26.5
VL26: C79.1, C81.A, JP27.1, R107.1, SJ54.1, U27.5
VL27: C82.1, C84.A, JP28.1, R111.1, SJ56.1, U28.5
VL28: C85.1, C87.A, JP29.1, R115.1, SJ58.1, U29.5
VL29: C88.1, C90.A, JP30.1, R119.1, SJ60.1, U30.5
VL30: C91.1, C93.A, JP31.1, R123.1, SJ62.1, U31.5
VL31: C94.1, C96.A, JP32.1, R127.1, SJ64.1, U32.5
VL32: C97.1, C99.A, JP33.1, R131.1, SJ66.1, U33.5
VL33: C100.1, C102.A, JP34.1, R135.1, SJ68.1, U34.5
VL34: C103.1, C105.A, JP35.1, R139.1, SJ70.1, U35.5

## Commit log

2014-03-03 Added initial README and LICENSE files
2014-03-03 Created schematic for breakout board
2014-03-05 Created initial layout
2014-03-05 Added SS text
2014-03-05 Added name on layout
2014-03-05 Replaced 4.7k INT pullup with 10k
2014-03-12 Rotated OSHW logo and added I2C address to sch and silk.
2014-04-15 Test commit with account
2014-05-14 Added separate VLED (VL) pin, connected VL and VCC with solder jumper and optional resistor. Re-did layout to support new features.
2014-05-14 Fixed text font and size on schematic
2014-05-30 Added skeleton library
2014-05-30 Renamed library SFE_APDS-9960 to SFE_APDS9960
2014-06-04 Created skeleton library and ProximityTest example
2014-06-07 Added first part of init function. Still need to finish default register values.
2014-06-08 Added init code for prox and ALS registers
2014-06-09 Added led gain control and photodiode mask methods
2014-07-03 Updated library. Can now read gesture FIFO.
2014-07-06 Added readGesture method. It sorta works.
2014-07-06 Fixed gesture sensing. Works like the Avago demo now.
2014-07-07 Fixed gesture return values for U/D/L/R and gestureTest example.
2014-07-15 Updated version number to v10 for reds
2014-07-15 created panel v10
2014-10-15 Fixed buffer overflow issue with block reads. This fixed the problems with reading NEAR and FAR gestures.
2014-10-23 Added outline for color sensing code
2014-10-23 Moved several get/set methods to public. Added power on/off method.
2014-10-24 Added methods to control light sensor and light sensor demo sketch.
2014-10-27 Added color (RGB) light sensing example.
2014-10-27 Added methods for controlling ambient light interrupt thresholds.
2014-10-28 Finished interrupt demos for the library.
2014-10-28 Readme added to library
2014-10-28 Fixed some misspellings in the library readme.
2014-11-03 Added PDF of schematic
2014-11-04 Updated READMEs with license and folder information
2014-11-05 Changed the names of files and Arduino libraries to contain 'SparkFun_' as a prefix
2014-11-07 Added known issue to library regarding the freezing on fast gestures
2014-11-14 Fixed freezing issue with fast swipes
2014-11-18 Added pinMode like to GestureTest.ino example to fix interrupt not working with some Arduinos.
2014-12-15 Suggestions For Possible Board Revision
    I have a few suggestions to make this board work better in my
    application.
    I'm a noob with GitHub, so I appologise if I'm doing this wrong.
    Changes:
    1) Rotate and relocate sensor as close as possible to edge of board.
    Reason: I want to be able to put this sensor board into an enclosure
2015-01-14 Implemented disableProximitySensor()
2015-02-04 Changed 4.7k resistors to proper 0603-RES package.
    This adds a small silkscreen dot under the resistor.
2015-02-05 Reverting to current board layout files
2015-04-26 Squashed 'Libraries/Arduino/' content from commit cb761c9
    git-subtree-dir: Libraries/Arduino
    git-subtree-split: cb761c9f0f9f36acc54a8502904df46fbca3fc06
2015-04-26 Updated to new library structure
2015-04-29 Part of the new arduino lib format updates
2015-04-29 commited
2015-04-29 Squashed 'Libraries/Arduino/' content from commit d35b342
    git-subtree-dir: Libraries/Arduino
    git-subtree-split: d35b342f01b4587b4a9401d6ab1262f9d95b321b
2015-05-13 Squashed 'Libraries/Arduino/' changes from d35b342..e60af2c
    git-subtree-dir: Libraries/Arduino
    git-subtree-split: e60af2cdf0042a4ac6cdcac1a4fe5b38b0d575b7
2015-05-13 Updating documentation, adding git attributes
2015-07-21 Squashed 'Libraries/Arduino/' changes from e60af2c..347a7d5
    347a7d5 Updating library name
    git-subtree-dir: Libraries/Arduino
    git-subtree-split: 347a7d55f1cf009bff58c28733b1f0bd2172092e
2017-04-15 Fix the GestureTest example
    Resolve the interrupt number with digitalPinToInterrupt() instead of
    hardcoding it to "0". This is the recommended method from
    https://www.arduino.cc/en/Reference/attachInterrupt
    It should work with post-2014 releases of any Arduino IDE version.
    (1.0.x, 1.5.x, 1.6.x)
    Also declare the isr_flag as volatile. It will not make a difference
2017-07-10 Put Arduino library in its own folder
    The previous folder structure did not match the installation instructions found in the library's README.md file. The previous library folder name "Arduino" was very unhelpful.
2018-04-16 new panel
2019-06-08 Add GY-9960LLC APDS-9960 sensor support
2019-10-30 Fix issues 23 and 26
    https://github.com/sparkfun/APDS-9960_RGB_and_Gesture_Sensor/issues/26
    https://github.com/sparkfun/APDS-9960_RGB_and_Gesture_Sensor/issues/23
2020-06-04 fixing issue with Wire usage, finicky compilers throwing warnings, issue where gesture recognition fails if one diode pair is activated, issue where gesture recognition sometimes crashed esp based sy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
2020-06-09 changed attachInterrupt for Wemos boards
2020-12-22 Adding WyoLum's Kicad version.
2021-06-20 Update interrupt pin
2022-08-17 Fixed requestFrom() compilation error

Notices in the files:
Hardware/Kicad/SparkFun_APDS-9960_RGB_and_Gesture_Sensor.sch:
Released under the Creative Commons Attribution Share-Alike 4.0 License
parts and their libraries:
SparkFun-Aesthetics: Licensing: Creative Commons ShareAlike 4.0 International - https://creativecommons.org/licenses/by-sa/4.0
